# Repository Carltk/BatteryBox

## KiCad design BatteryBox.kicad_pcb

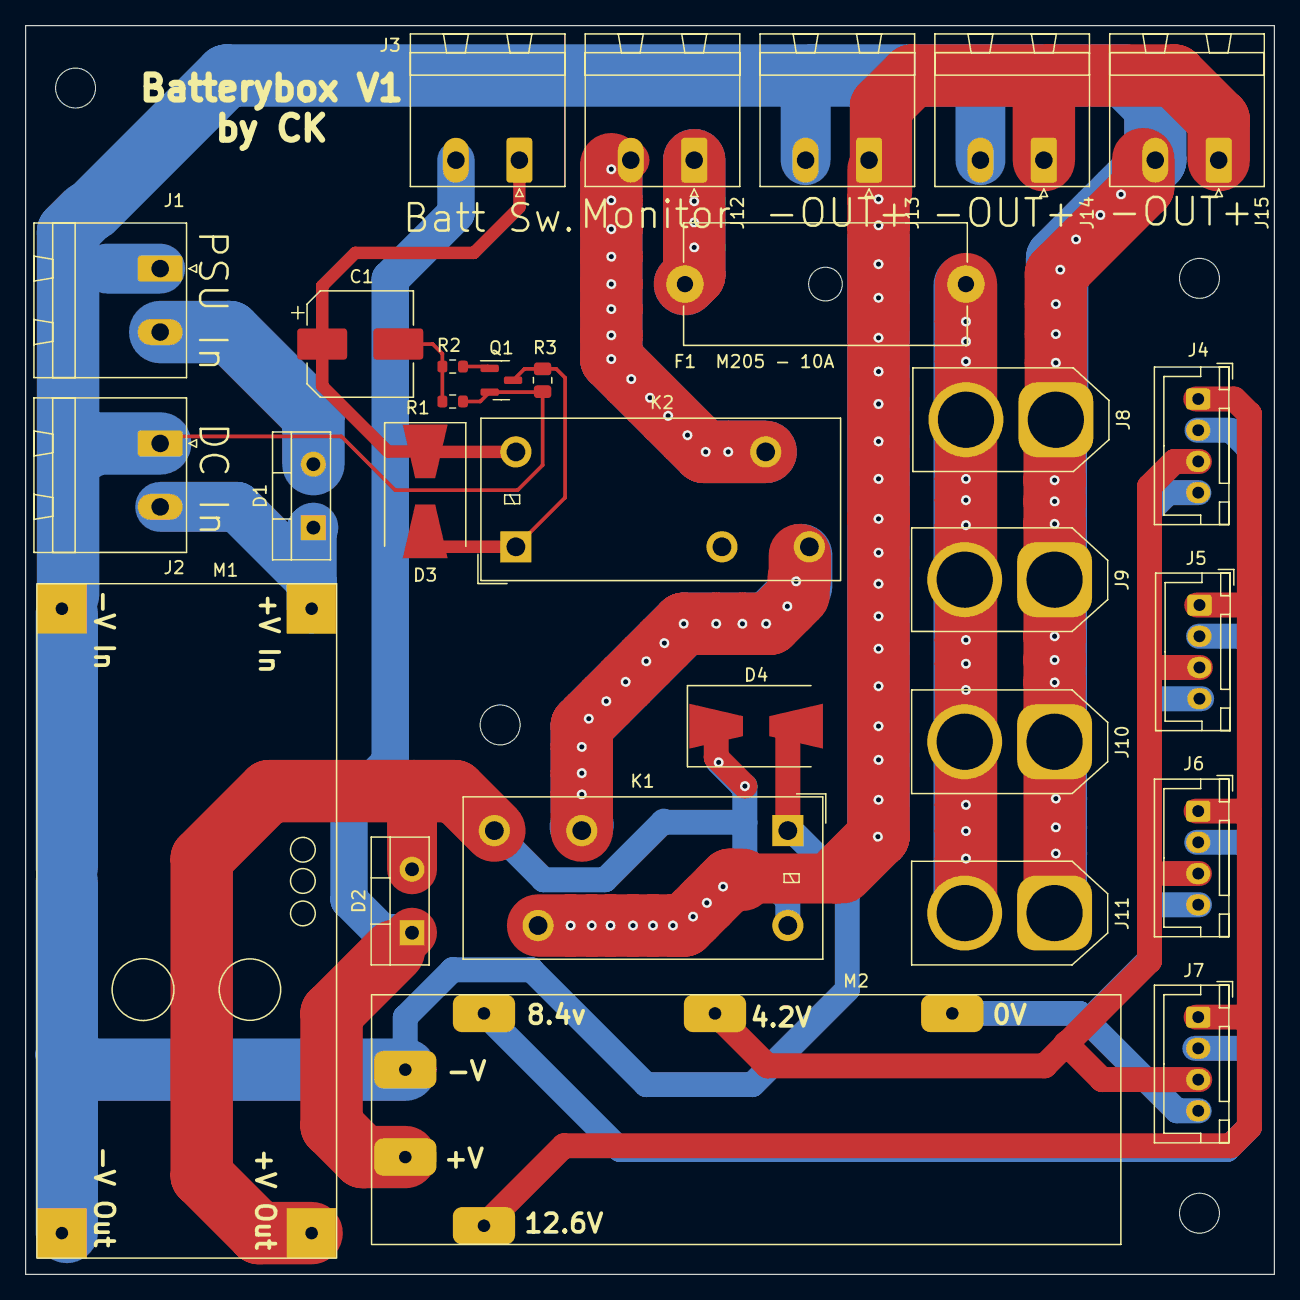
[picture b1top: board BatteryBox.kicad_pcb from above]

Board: 2 copper layers, 100.0 x 100.0 mm, 33 parts (0 on the bottom side), 18 nets.

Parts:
C1: 47uF 35V Electro; CP_Elec_8x6.5
D1, D2: D_Schottky; TO-220-2_Vertical
D3, D4: D_Schottky; D_SMB-SMC_Universal_Handsoldering
F1: M205 - 10A; Fuseholder_Cylinder-5x20mm_Schurter_0031_8201_Horizontal_Op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
H1, H2, H3, H4: MountingHole; MountingHole_3.2mm_M3
J1, J2, J3, J12, J13, J14, J15: Conn_01x02; PhoenixContact_MSTBA_2,5_2-G-5,08_1x02_P5.08mm_Horizontal
J4, J5, J6, J7: Conn_01x04; JST_XH_B4B-XH-A_1x04_P2.50mm_Vertical
J8, J9, J10, J11: Conn_01x02; AMASS_XT60-M_1x02_P7.20mm_Vertical
K1, K2: SANYOU_SRD_Form_C; Relay_SPDT_Panasonic_JW1_FormC
M1: Regulator_Module; PSU_Module
M2: BMS_Module
Q1: BC817; SOT-23
R1: 2K2; R_0603_1608Metric
R2: 1K; R_0603_1608Metric
R3: 150R 0.25W; R_0805_2012Metric

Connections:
GND: D4.2 (A), J1.1, J2.1, J8.1, J9.1, J10.1, J11.1, J13.2, J14.2, J15.2, K1.1, M1.2 (In-), M1.4 (Out-), M2.2 (-V), Q1.2 (E), R1.1, R3.2
unnamed: C1.1, D3.1 (K), J3.1, K2.8
unnamed: C1.2, R1.2, R2.1
unnamed: D1.1 (K), J2.2, M1.1 (In+)
unnamed: D1.2 (A), J1.2
unnamed: D2.1 (K), J3.2, M2.1 (+V)
unnamed: D2.2 (A), D4.1 (K), K1.4, K1.8, M1.3 (Out+)
unnamed: D3.2 (A), K2.1, Q1.3 (C), R3.1
unnamed: F1.1, J8.2, J9.2, J10.2, J11.2
unnamed: F1.2, J12.1
unnamed: J4.1, J5.1, J6.1, J7.1, M2.6 (B_12)
unnamed: J4.2, J5.2, J6.2, J7.2, M2.5 (B_8)
unnamed: J4.3, J5.3, J6.3, J7.3, M2.4 (B_4)
unnamed: J4.4, J5.4, J6.4, J7.4, M2.3 (B_0)
unnamed: J12.2, K2.6
unnamed: J13.1, J14.1, J15.1, K1.6
unnamed: K1.2, K2.4
unnamed: Q1.1 (B), R2.2

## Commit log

2022-09-13 Finalising PCB layout. Needs final component puchase and footprint check.
